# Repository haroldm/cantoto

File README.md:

# cantoto

Hardware and firmware to convert infotaimment CAN messages.

This project is inspired from [canbox](https://github.com/smartgauges/canbox) and was originally a [fork](https://github.com/haroldm/canbox) of it.

Messages converted:
* Illumination (autoradio dark or light mode) is converted to a 0V/12V binary signal
* Accessory power is converted to a 0V/12V binary signal
* Steering wheel media keys are converted to a voltage between 0 and 5v that will be sensed by the radio

Compatible vehicles: Audi A3 8P facelift (and probably other cars on the PQ35 platform).
Compatible radios: ATOTO F7 (and probably most third-party radio)

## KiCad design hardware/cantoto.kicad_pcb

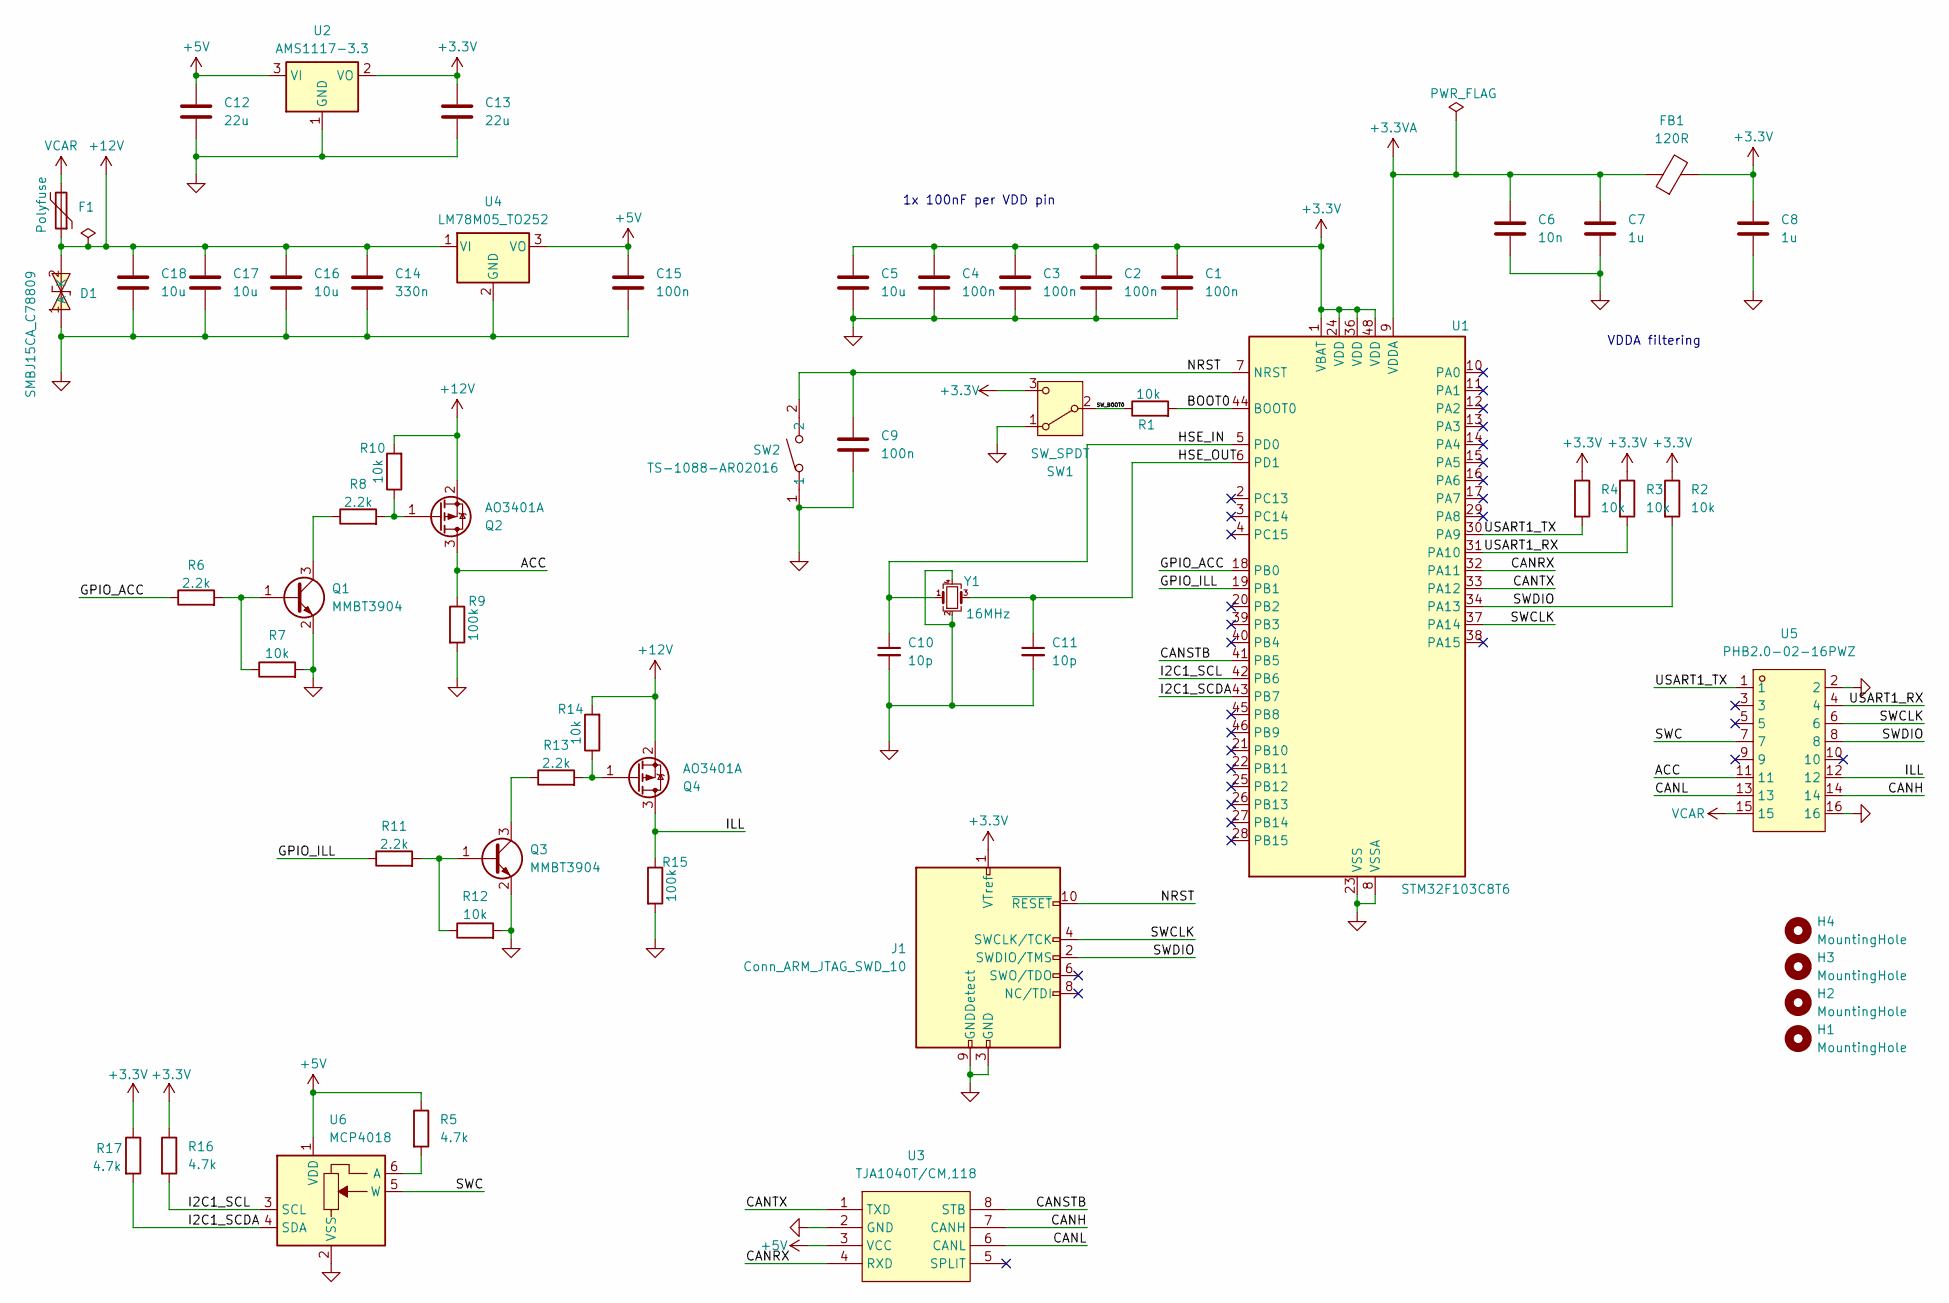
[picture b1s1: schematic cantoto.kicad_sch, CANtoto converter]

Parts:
C1, C2, C3, C4, C9: 100n; C_0402_1005Metric
C5: 10u; C_0603_1608Metric
C6: 10n; C_0402_1005Metric
C7, C8: 1u; C_0402_1005Metric
C10, C11: 10p; C_0402_1005Metric
C12, C13: 22u; C_0805_2012Metric
C14: 330n; C_0805_2012Metric
C15: 100n; C_0805_2012Metric
C16, C17, C18: 10u; C_1206_3216Metric
D1: SMBJ15CA_C78809; SMB_L4.6-W3.6-LS5.3-BI; LCSC Part C78809
F1: Polyfuse; Fuse_1812_4532Metric
FB1: 120R; L_0603_1608Metric
H1, H2, H3, H4: MountingHole; MountingHole_3mm
J1: Conn_ARM_JTAG_SWD_10; PinHeader_2x05_P1.27mm_Vertical_SMD
Q1, Q3: MMBT3904; SOT-23
Q2, Q4: AO3401A; SOT-23
R1, R2, R3, R4, R7, R10, R12, R14: 10k; R_0402_1005Metric
R5, R16, R17: 4.7k; R_0402_1005Metric
R6, R8, R11, R13: 2.2k; R_0402_1005Metric
R9, R15: 100k; R_0402_1005Metric
SW1: SW_SPDT; SW_SPDT_PCM12
SW2: TS-1088-AR02016; SW-SMD_L3.9-W3.0-P4.45; LCSC Part C720477
U1: STM32F103C8T6; LQFP-48_7x7mm_P0.5mm
U2: AMS1117-3.3; SOT-223-3_TabPin2
U3: TJA1040T/CM,118; SOIC-8_L5.0-W4.0-P1.27-LS6.0-BL; LCSC Part C6951
U4: LM78M05_TO252; TO-252-2
U5: PHB2.0-02-16PWZ; CONN-TH_16P-P2.00_S16B-PADSS-1; LCSC Part C19077320
U6: MCP4018; SOT-363_SC-70-6
Y1: 16MHz; Crystal_SMD_3225-4Pin_3.2x2.5mm

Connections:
+3.3V: C1.1, C2.1, C3.1, C4.1, C5.1, C8.1, C13.1, FB1.2, J1.1 (VTref), R2.1, R3.1, R4.1, R16.1, R17.1, SW1.3 (C), U1.1 (VBAT), U1.24 (VDD), U1.36 (VDD), U1.48 (VDD), U2.2 (VO)
+3.3VA: C6.1, C7.1, FB1.1, U1.9 (VDDA)
+5V: C12.1, C15.1, R5.1, U2.3 (VI), U3.3 (VCC), U4.3 (VO), U6.1 (VDD)
+12V: C14.1, C16.1, C17.1, C18.1, D1.2 (A), F1.1, Q2.2 (S), Q4.2 (S), R10.2, R14.2, U4.1 (VI)
/ACC: Q2.3 (D), R9.1, U5.11
/BOOT0: R1.2, U1.44 (BOOT0)
/CANH: U3.7 (CANH), U5.14
/CANL: U3.6 (CANL), U5.13
/CANRX: U1.32 (PA11), U3.4 (RXD)
/CANSTB: U1.41 (PB5), U3.8 (STB)
/CANTX: U1.33 (PA12), U3.1 (TXD)
/GPIO_ACC: R6.1, U1.18 (PB0)
/GPIO_ILL: R11.1, U1.19 (PB1)
/HSE_IN: C10.1, U1.5 (PD0), Y1.1
/HSE_OUT: C11.1, U1.6 (PD1), Y1.3
/I2C1_SCDA: R17.2, U1.43 (PB7), U6.4 (SDA)
/I2C1_SCL: R16.2, U1.42 (PB6), U6.3 (SCL)
/ILL: Q4.3 (D), R15.1, U5.12
/NRST: C9.1, J1.10 (~RESET), SW2.2, U1.7 (NRST)
/SWC: U5.7, U6.5 (W)
/SWCLK: J1.4 (SWCLK/TCK), U1.37 (PA14), U5.6
/SWDIO: J1.2 (SWDIO/TMS), R2.2, U1.34 (PA13), U5.8
/SW_BOOT0: R1.1, SW1.2 (B)
/USART1_RX: R3.2, U1.31 (PA10), U5.4
/USART1_TX: R4.2, U1.30 (PA9), U5.1
GND: C1.2, C2.2, C3.2, C4.2, C5.2, C6.2, C7.2, C8.2, C9.2, C10.2, C11.2, C12.2, C13.2, C14.2, C15.2, C16.2, C17.2, C18.2, D1.1 (K), J1.3 (GND), J1.5 (GND), J1.9 (GNDDetect), Q1.2 (E), Q3.2 (E), R7.2, R9.2, R12.2, R15.2, SW1.1 (A), SW2.1, U1.8 (VSSA), U1.23 (VSS), U1.35 (VSS), U1.47 (VSS), U2.1 (GND), U3.2 (GND), U4.2 (GND), U5.2, U5.16, U6.2 (VSS), Y1.2, Y1.4
unnamed: Q1.1 (B), R6.2, R7.1
unnamed: Q1.3 (C), R8.1
unnamed: Q2.1 (G), R8.2, R10.1
unnamed: Q3.1 (B), R11.2, R12.1
unnamed: Q3.3 (C), R13.1
unnamed: Q4.1 (G), R13.2, R14.1
unnamed: R5.2, U6.6 (A)
VCAR: F1.2, U5.15

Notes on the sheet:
VDDA filtering
1x 100nF per VDD pin

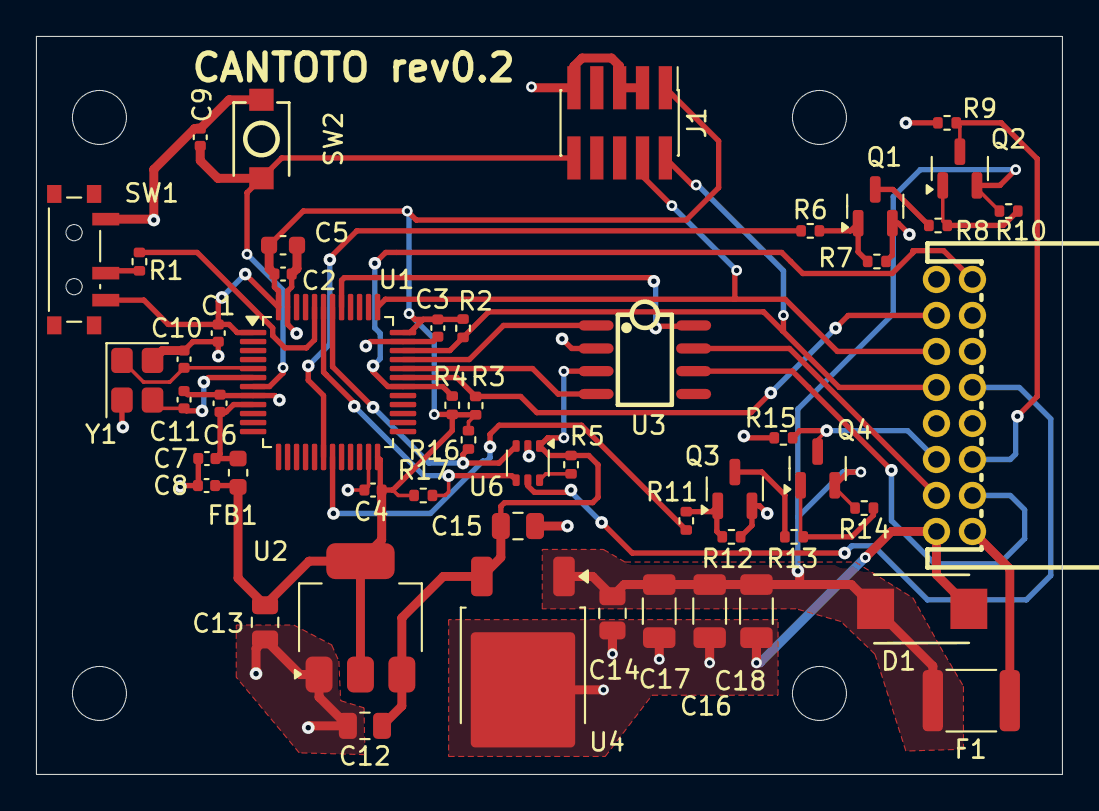
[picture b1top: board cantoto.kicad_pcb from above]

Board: 2 copper layers, 57.0 x 41.0 mm, 56 parts (0 on the bottom side), 34 nets.

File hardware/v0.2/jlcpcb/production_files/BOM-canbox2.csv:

Comment,Designator,Footprint,LCSC,Quantity
10u,"C16,C17,C18",C_1206_3216Metric,C13585,3
16MHz,Y1,Crystal_SMD_3225-4Pin_3.2x2.5mm,C13738,1
120R,FB1,L_0603_1608Metric,C14709,1
AO3401A,"Q2,Q4",SOT-23,C15127,2
10n,C6,C_0402_1005Metric,C15195,1
100n,"C1,C2,C3,C4,C9",C_0402_1005Metric,C1525,5
330n,C14,C_0805_2012Metric,C1740,1
PHB2.0-02-16PWZ,U5,CONN-TH_16P-P2.00_S16B-PADSS-1,C19077320,1
10u,C5,C_0603_1608Metric,C19702,1
MMBT3904,"Q1,Q3",SOT-23,C20526,2
100k,"R15,R9",R_0402_1005Metric,C25741,2
10k,"R1,R10,R12,R14,R2,R3,R4,R7",R_0402_1005Metric,C25744,8
2.2k,"R11,R13,R6,R8",R_0402_1005Metric,C25879,4
4.7k,"R16,R17,R5",R_0402_1005Metric,C25900,3
100n,C15,C_0805_2012Metric,C28233,1
10p,"C10,C11",C_0402_1005Metric,C32949,2
22u,"C12,C13",C_0805_2012Metric,C45783,2
1u,"C7,C8",C_0402_1005Metric,C52923,2
LM78M05_TO252,U4,TO-252-2,C58069,1
AMS1117-3.3,U2,SOT-223-3_TabPin2,C6186,1
"TJA1040T/CM,118",U3,SOIC-8_L5.0-W4.0-P1.27-LS6.0-BL,C6951,1
TS-1088-AR02016,SW2,SW-SMD_L3.9-W3.0-P4.45,C720477,1
SMBJ15CA_C78809,D1,SMB_L4.6-W3.6-LS5.3-BI,C78809,1
STM32F103C8T6,U1,LQFP-48_7x7mm_P0.5mm,C8734,1
Conn_ARM_JTAG_SWD_10,J1,PinHeader_2x05_P1.27mm_Vertical_SMD,,1
SW_SPDT,SW1,SW_SPDT_PCM12,,1
MCP4018,U6,SOT-363_SC-70-6,,1
Polyfuse,F1,Fuse_1812_4532Metric,,1

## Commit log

2025-06-26 CAN bring up
2025-06-26 Initial commit: set up dev env with PlatformIO
2025-06-26 Add clang-format pre-commit hook and format files.
2025-06-26 Add CAN parser and timer setup
2025-06-26 Check that pre-commit passes without error on all files
2025-06-26 Add a basic control and debug interface on USART
2025-06-28 Add kicad project and v0.2 build files
2025-06-28 Move code to firmware/
2025-06-28 Add control of GPIO and digipot.
    Also added some debugging logic.
2025-06-28 Rename kicad project
2025-06-28 Add rev0.2 marking to silkscreen
